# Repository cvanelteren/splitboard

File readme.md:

# Table of Contents

1.  [Welcome to Splitboard](#orge151485)
2.  [Features](#orgcb3fcca)
3.  [Know projects](#org8324adf)

# Welcome to Splitboard

Keyboard firmware written for the  esp32. I wanted to have a
bluetooth  split  keyboard  for  a while  so  I  wrote  this
firmware. The software takes  heavy inspiration from the [QMK
firmware](https://docs.qmk.fm/#/), and was developed using Platformio.

# Features

-   [X] Split communication over esp<sub>now</sub>
-   [X] Layer support
    -   Up to 16 layers
-   [X] LED support through [FastLED](https://github.com/FastLED)
-   [X] OLED support through [U8G2](https://github.com/olikraus/u8g2)
-   [X] Layer tap functionality
    -   Tap for keycode, hold for layer switch
-   [ ] Space cadet keys
    -   Shift when tapped, shift was modifier.

# Know projects

-   [Elanor](https://github.com/cvanelteren/Elanor)

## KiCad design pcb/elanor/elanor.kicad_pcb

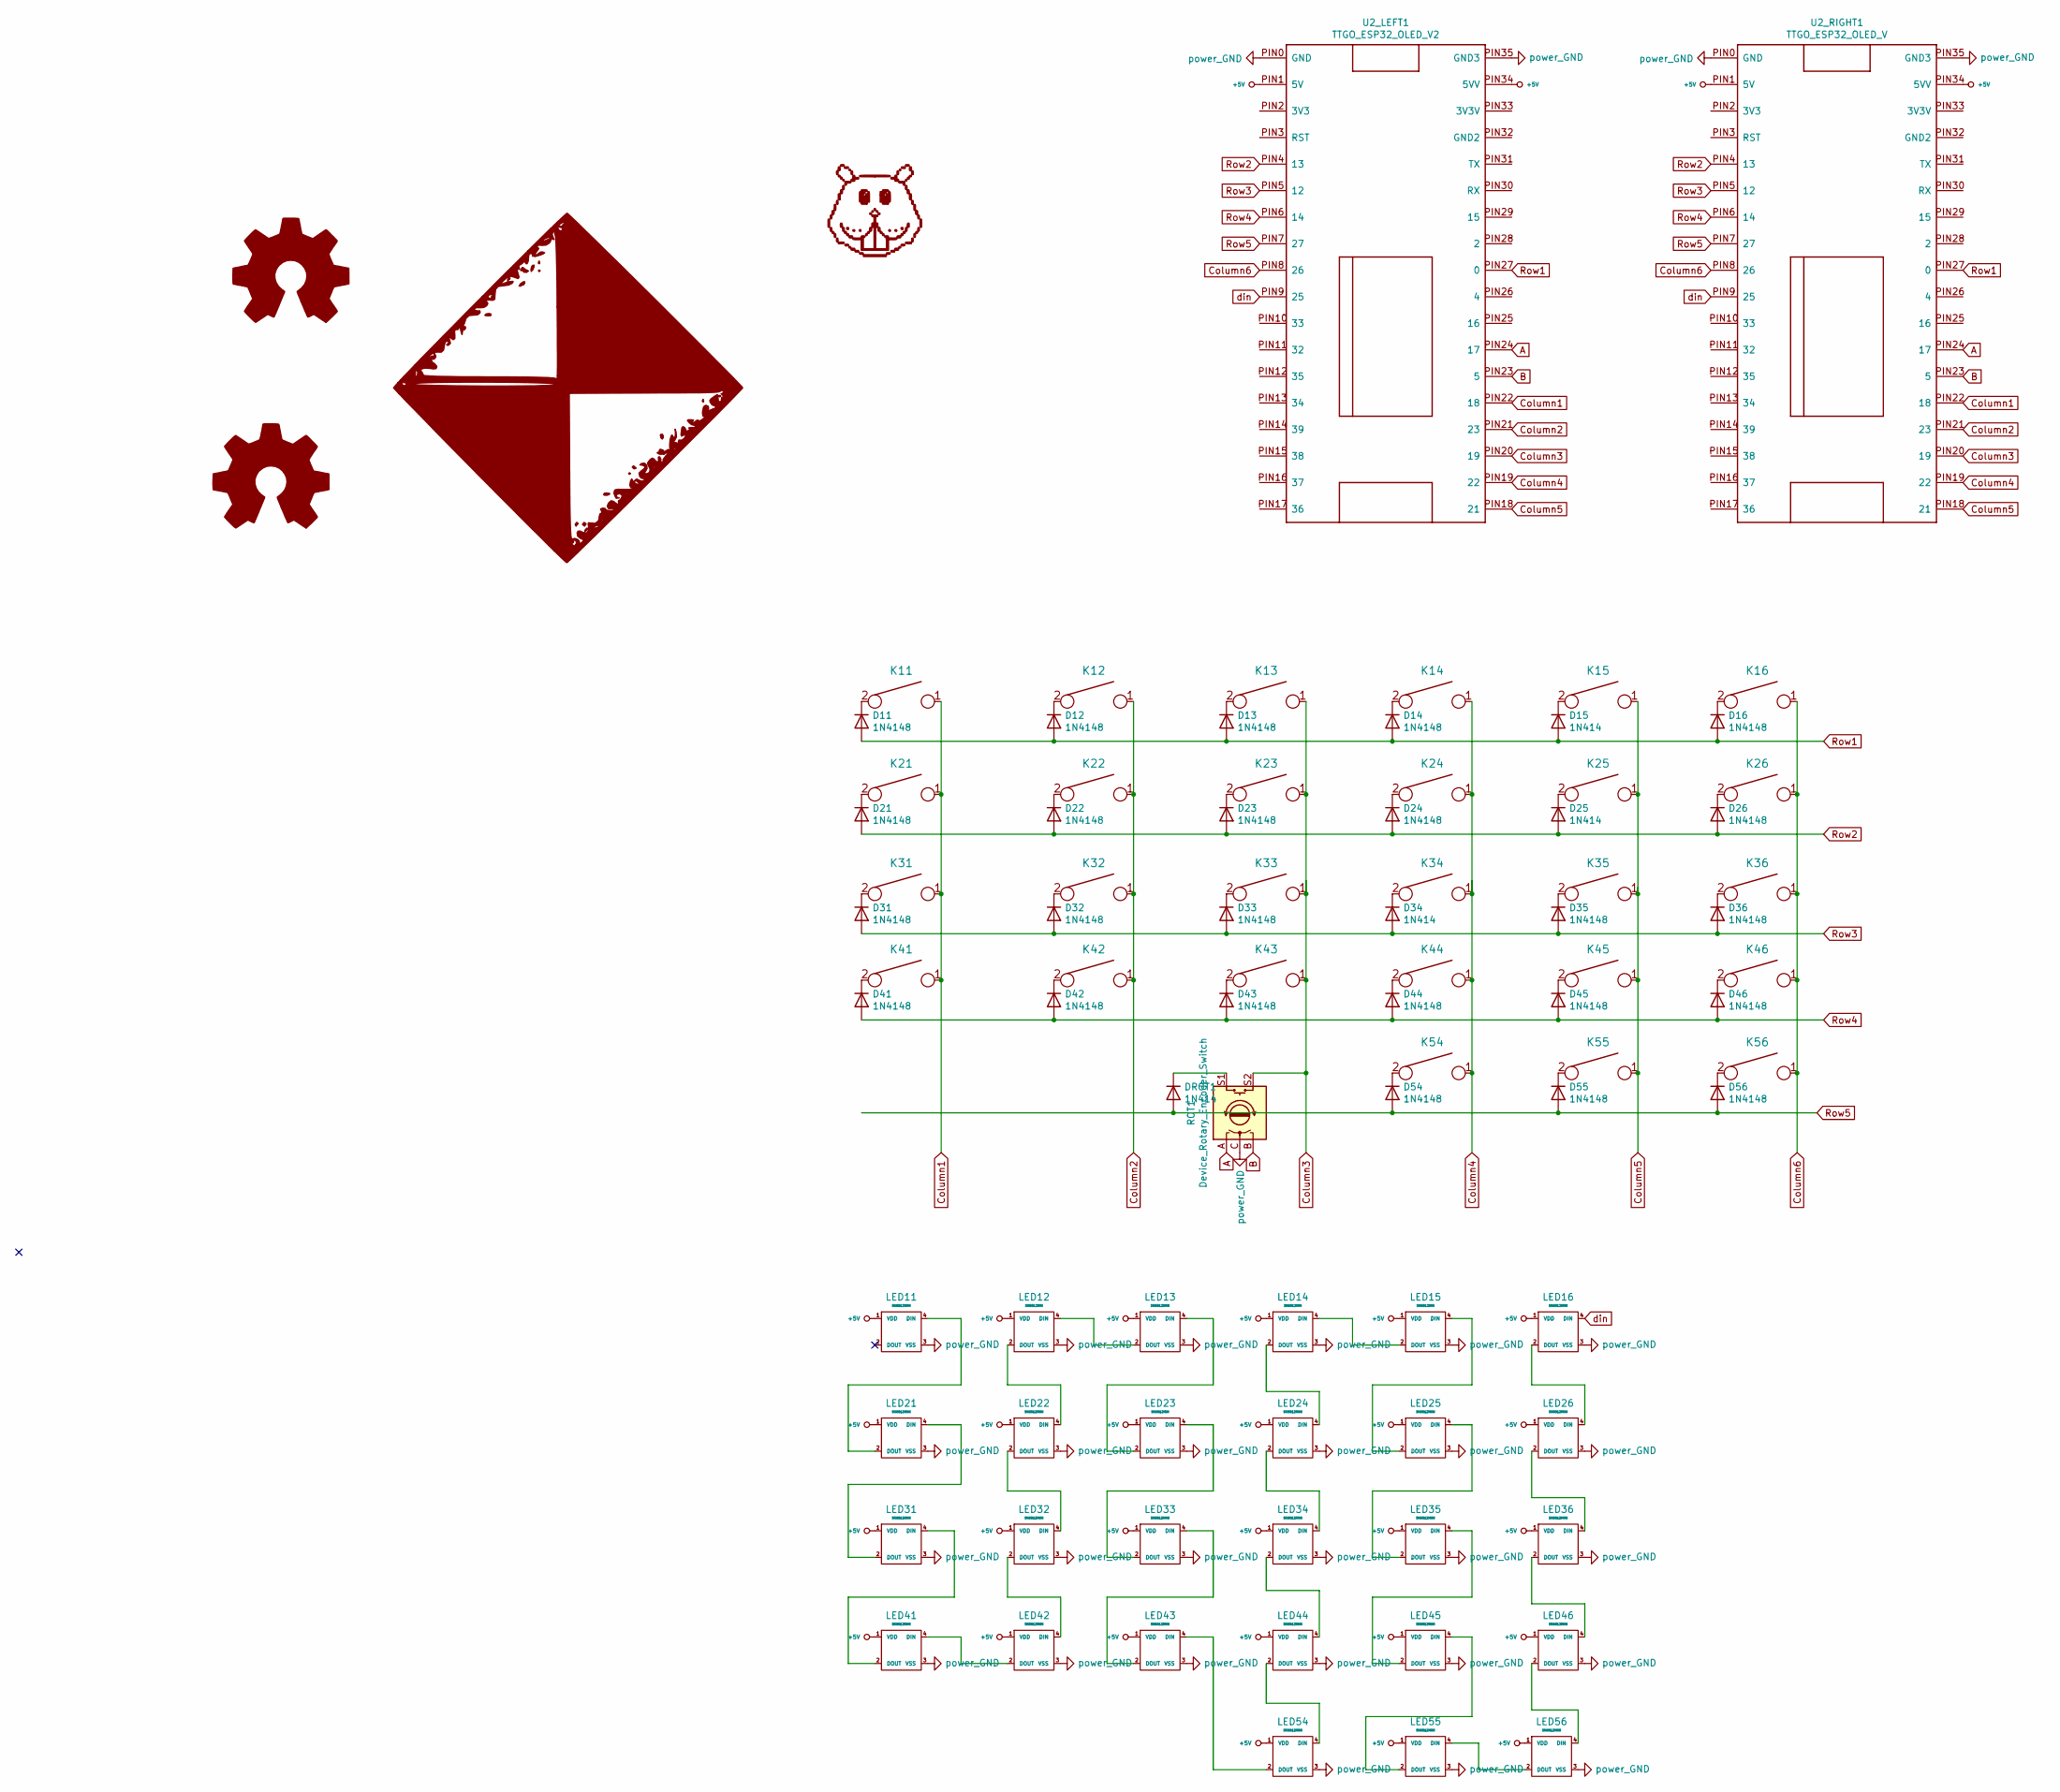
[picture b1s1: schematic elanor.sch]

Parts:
BOARD_LOGO1: LOGO; cve_logo_neg
D11, D12, D13, D14, D16, D21, D22, D23, D24, D26, D31, D32, D33, D35, D36, D41, D42, D43, D44, D45, D46, D54, D55, D56: 1N4148; D3_TH_SMD_v2
D15, D25, D34: 1N414; D3_TH_SMD_v2
DROT1: 1N414; D3_TH_SMD_v2
K11, K12, K13, K14, K15, K16, K21, K22, K23, K24, K25, K26, K31, K32, K33, K34, K35, K36, K41, K42, K43, K44, K45, K46, K54: key; CherryMX_MidHeight_Hotswap_ME
K55: key; CherryMX_MidHeight_Hotswap1.25v
K56: key; CherryMX_MidHeight_Hotswap1.5v
LED11, LED13, LED16, LED21, LED22, LED24, LED25, LED26, LED31, LED32, LED33, LED34, LED35, LED36, LED41, LED42, LED43, LED44, LED45, LED46, LED54, LED55, LED56: SK6812MINI; SK6812_double_sided_no_hole
LED12, LED14, LED15, LED23: SK6812MIN; SK6812_double_sided_no_hole
ROT1: Device_Rotary_Encoder_Switch; RotaryEncoder_Alps_EC11E-Switch_Vertical_H20mm
U2_LEFT1: TTGO_ESP32_OLED_V2; ESP32_TTGO_V2
U2_RIGHT1: TTGO_ESP32_OLED_V; ESP32_TTGO_V2
beaver1: FL; beaver_fiona

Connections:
+5V: LED11.1 (VDD), LED12.1 (VDD), LED13.1 (VDD), LED14.1 (VDD), LED15.1 (VDD), LED16.1 (VDD), LED21.1 (VDD), LED22.1 (VDD), LED23.1 (VDD), LED24.1 (VDD), LED25.1 (VDD), LED26.1 (VDD), LED31.1 (VDD), LED32.1 (VDD), LED33.1 (VDD), LED34.1 (VDD), LED35.1 (VDD), LED36.1 (VDD), LED41.1 (VDD), LED42.1 (VDD), LED43.1 (VDD), LED44.1 (VDD), LED45.1 (VDD), LED46.1 (VDD), LED54.1 (VDD), LED55.1 (VDD), LED56.1 (VDD), U2_LEFT1.PIN1 (5V), U2_LEFT1.PIN34 (5VV), U2_RIGHT1.PIN1 (5V), U2_RIGHT1.PIN34 (5VV)
A: ROT1.A, U2_LEFT1.PIN24 (17), U2_RIGHT1.PIN24 (17)
B: ROT1.B, U2_LEFT1.PIN23 (5), U2_RIGHT1.PIN23 (5)
Column1: K11.1, K21.1, K31.1, K41.1, U2_LEFT1.PIN22 (18), U2_RIGHT1.PIN22 (18)
Column2: K12.1, K22.1, K32.1, K42.1, U2_LEFT1.PIN21 (23), U2_RIGHT1.PIN21 (23)
Column3: K13.1, K23.1, K33.1, K43.1, ROT1.S2, U2_LEFT1.PIN20 (19), U2_RIGHT1.PIN20 (19)
Column4: K14.1, K24.1, K34.1, K44.1, K54.1, U2_LEFT1.PIN19 (22), U2_RIGHT1.PIN19 (22)
Column5: K15.1, K25.1, K35.1, K45.1, K55.1, U2_LEFT1.PIN18 (21), U2_RIGHT1.PIN18 (21)
Column6: K16.1, K26.1, K36.1, K46.1, K56.1, U2_LEFT1.PIN8 (26), U2_RIGHT1.PIN8 (26)
GND: LED11.3 (VSS), LED12.3 (VSS), LED13.3 (VSS), LED14.3 (VSS), LED15.3 (VSS), LED16.3 (VSS), LED21.3 (VSS), LED22.3 (VSS), LED23.3 (VSS), LED24.3 (VSS), LED25.3 (VSS), LED26.3 (VSS), LED31.3 (VSS), LED32.3 (VSS), LED33.3 (VSS), LED34.3 (VSS), LED35.3 (VSS), LED36.3 (VSS), LED41.3 (VSS), LED42.3 (VSS), LED43.3 (VSS), LED44.3 (VSS), LED45.3 (VSS), LED46.3 (VSS), LED54.3 (VSS), LED55.3 (VSS), LED56.3 (VSS), ROT1.C, U2_LEFT1.PIN0 (GND), U2_LEFT1.PIN35 (GND3), U2_RIGHT1.PIN0 (GND), U2_RIGHT1.PIN35 (GND3)
unnamed: D11.1 (K), K11.2
unnamed: D12.1 (K), K12.2
unnamed: D13.1 (K), K13.2
unnamed: D14.1 (K), K14.2
unnamed: D15.1 (K), K15.2
unnamed: D16.1 (K), K16.2
unnamed: D21.1 (K), K21.2
unnamed: D22.1 (K), K22.2
unnamed: D23.1 (K), K23.2
unnamed: D24.1 (K), K24.2
unnamed: D25.1 (K), K25.2
unnamed: D26.1 (K), K26.2
unnamed: D31.1 (K), K31.2
unnamed: D32.1 (K), K32.2
unnamed: D33.1 (K), K33.2
unnamed: D34.1 (K), K34.2
unnamed: D35.1 (K), K35.2
unnamed: D36.1 (K), K36.2
unnamed: D41.1 (K), K41.2
unnamed: D42.1 (K), K42.2
unnamed: D43.1 (K), K43.2
unnamed: D44.1 (K), K44.2
unnamed: D45.1 (K), K45.2
unnamed: D46.1 (K), K46.2
unnamed: D54.1 (K), K54.2
unnamed: D55.1 (K), K55.2
unnamed: D56.1 (K), K56.2
unnamed: DROT1.1 (K), ROT1.S1
unnamed: LED11.4 (DIN), LED21.2 (DOUT)
unnamed: LED12.2 (DOUT), LED22.4 (DIN)
unnamed: LED12.4 (DIN), LED13.2 (DOUT)
unnamed: LED13.4 (DIN), LED23.2 (DOUT)
unnamed: LED14.2 (DOUT), LED24.4 (DIN)
unnamed: LED14.4 (DIN), LED15.2 (DOUT)
unnamed: LED15.4 (DIN), LED25.2 (DOUT)
unnamed: LED16.2 (DOUT), LED26.4 (DIN)
unnamed: LED21.4 (DIN), LED31.2 (DOUT)
unnamed: LED22.2 (DOUT), LED32.4 (DIN)
unnamed: LED23.4 (DIN), LED33.2 (DOUT)
unnamed: LED24.2 (DOUT), LED34.4 (DIN)
unnamed: LED25.4 (DIN), LED35.2 (DOUT)
unnamed: LED26.2 (DOUT), LED36.4 (DIN)
unnamed: LED31.4 (DIN), LED41.2 (DOUT)
unnamed: LED32.2 (DOUT), LED42.4 (DIN)
unnamed: LED33.4 (DIN), LED43.2 (DOUT)
unnamed: LED34.2 (DOUT), LED44.4 (DIN)
unnamed: LED35.4 (DIN), LED45.2 (DOUT)
unnamed: LED36.2 (DOUT), LED46.4 (DIN)
unnamed: LED41.4 (DIN), LED42.2 (DOUT)
unnamed: LED43.4 (DIN), LED54.2 (DOUT)
unnamed: LED44.2 (DOUT), LED54.4 (DIN)
unnamed: LED45.4 (DIN), LED55.2 (DOUT)
unnamed: LED46.2 (DOUT), LED56.4 (DIN)
unnamed: LED55.4 (DIN), LED56.2 (DOUT)
Row1: D11.2 (A), D12.2 (A), D13.2 (A), D14.2 (A), D15.2 (A), D16.2 (A), U2_LEFT1.PIN27 (0), U2_RIGHT1.PIN27 (0)
Row2: D21.2 (A), D22.2 (A), D23.2 (A), D24.2 (A), D25.2 (A), D26.2 (A), U2_LEFT1.PIN4 (13), U2_RIGHT1.PIN4 (13)
Row3: D31.2 (A), D32.2 (A), D33.2 (A), D34.2 (A), D35.2 (A), D36.2 (A), U2_LEFT1.PIN5 (12), U2_RIGHT1.PIN5 (12)
Row4: D41.2 (A), D42.2 (A), D43.2 (A), D44.2 (A), D45.2 (A), D46.2 (A), U2_LEFT1.PIN6 (14), U2_RIGHT1.PIN6 (14)
Row5: D54.2 (A), D55.2 (A), D56.2 (A), DROT1.2 (A), U2_LEFT1.PIN7 (27), U2_RIGHT1.PIN7 (27)
din: LED16.4 (DIN), U2_LEFT1.PIN9 (25), U2_RIGHT1.PIN9 (25)

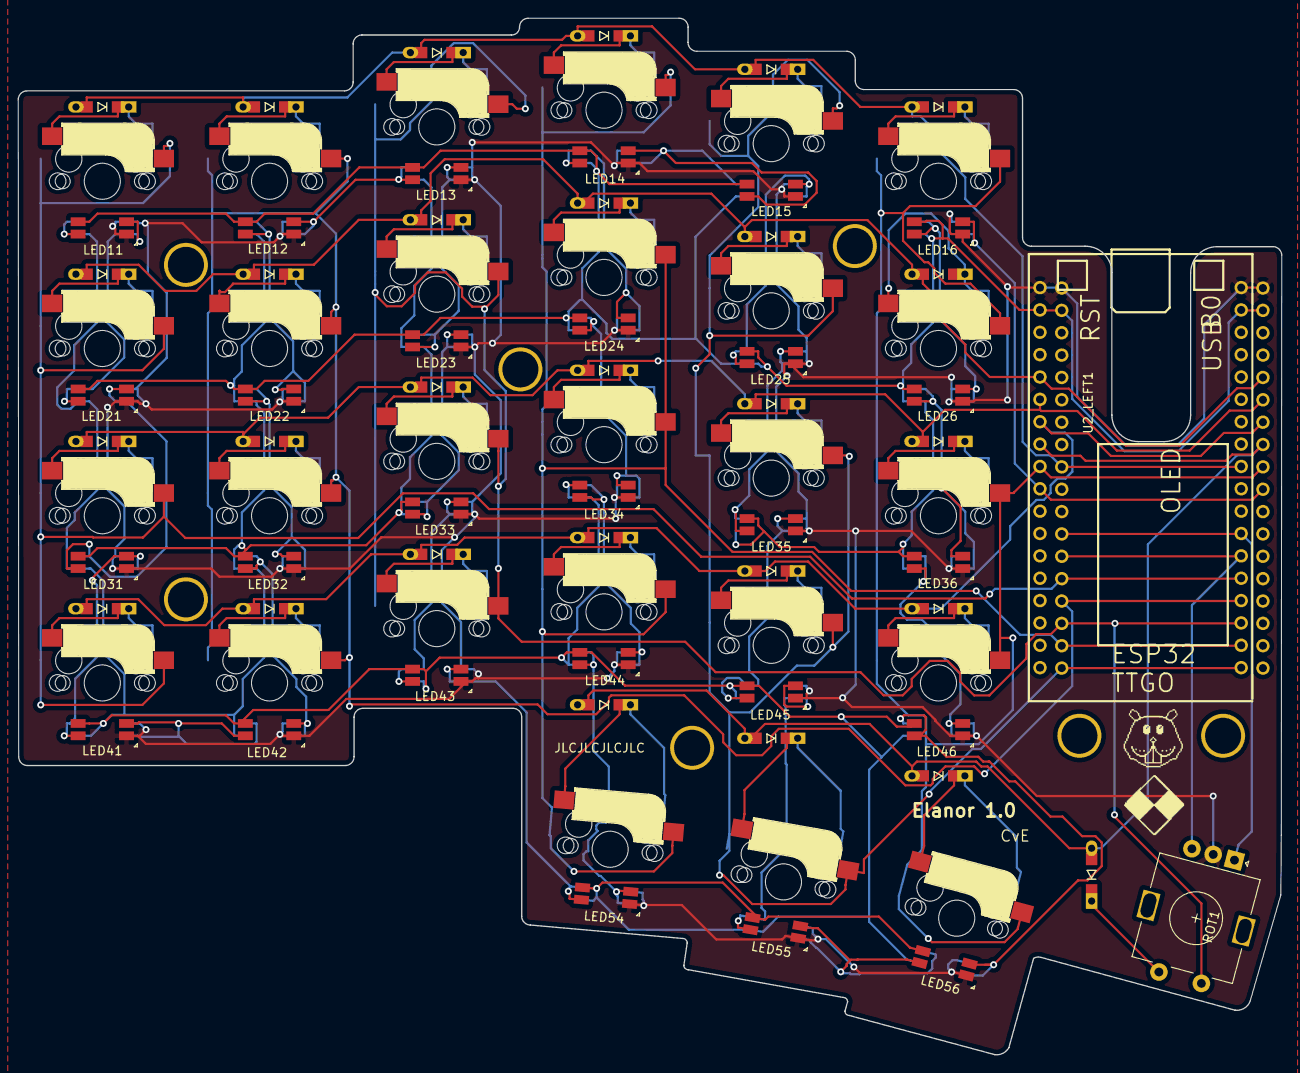
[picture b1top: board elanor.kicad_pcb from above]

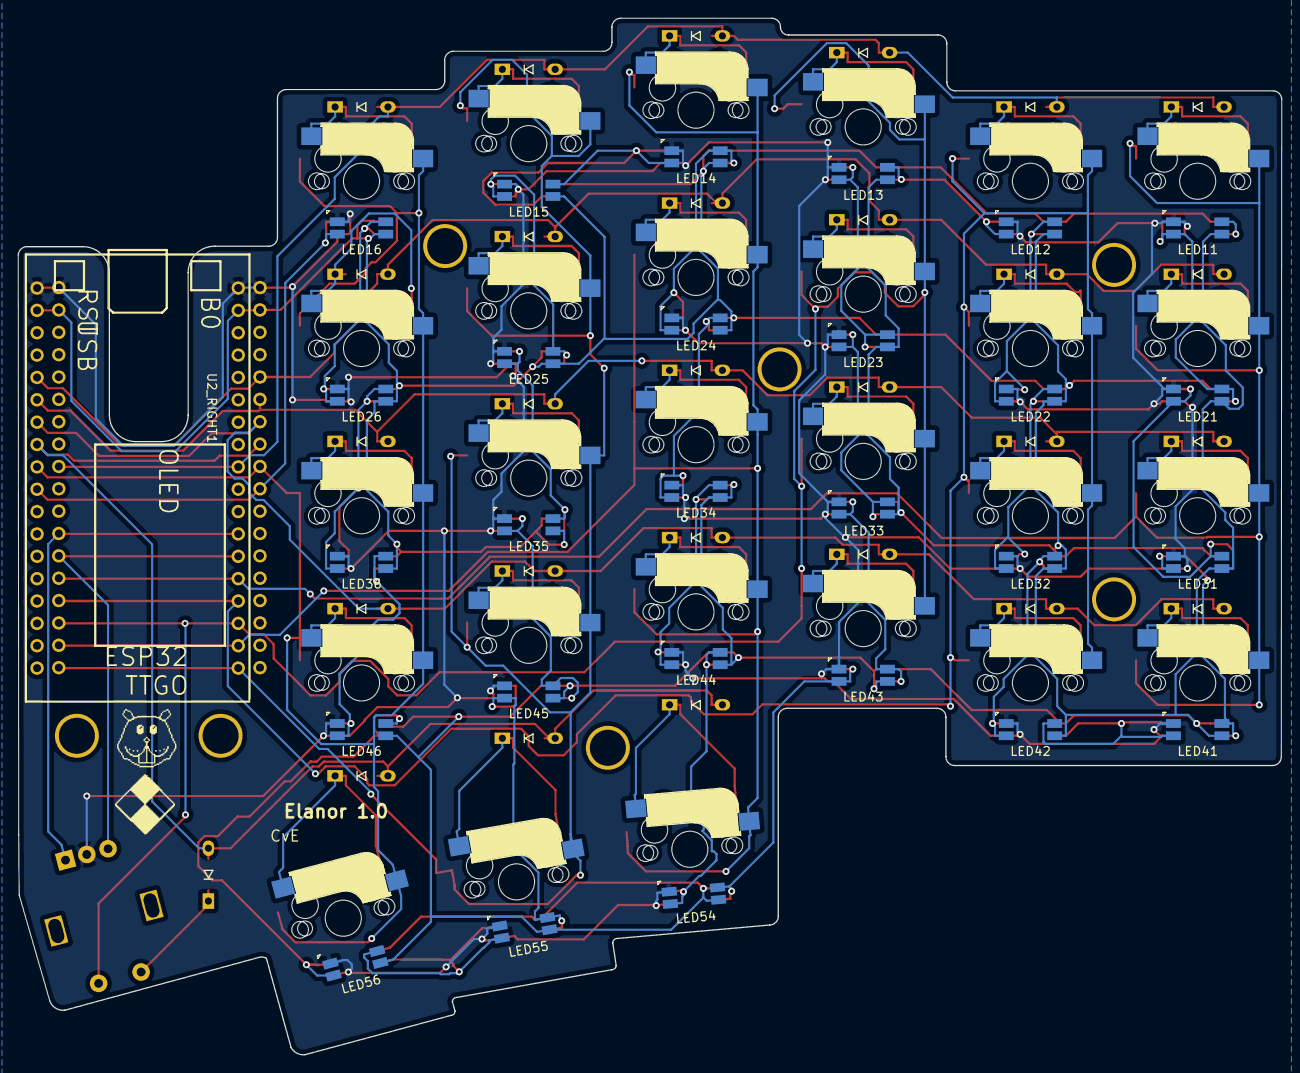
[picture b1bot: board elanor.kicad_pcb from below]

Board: 2 copper layers, 143.5 x 117.8 mm, 96 parts (3 on the bottom side), 70 nets.

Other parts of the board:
BOARD_LOGO1#2: CvE; cve_logo_neg
C11: column 5; LEGO_HOLE
C15: column3; LEGO_HOLE
C33: column 4; LEGO_HOLE
C51: column2; LEGO_HOLE
C55: column1; LEGO_HOLE
EC11: EC11; LEGO_HOLE
EC12: EC12; LEGO_HOLE
beaver1#2: FL; beaver_fiona

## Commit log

2021-04-29 all components working!
2021-07-04 working on remote_now
2021-07-04 added esp-now mesh; need to correct static variables
2021-07-04 removed logs; added basic cli
2021-07-04 added licencse
2021-07-09 removing ble
2021-07-11 working button press
2021-07-17 added merge function; broken
2021-07-26 working on press and release
2021-07-26 switches presses and releases are registered; switch was hooked wrong :P
2021-07-26 working shift key!
2021-07-30 added rotary encoder class
2021-08-08 added rotary encoder; added deep sleep
2021-08-08 removed decoder.py
2021-08-08 cleaned up repo
2021-08-08 rotary encoder now controls volume
2021-08-10 ble sending repeated keys?
2021-08-11 weird bug is gone, not sure what caused it
2021-08-16 regular update
2021-08-16 added row col for print
2021-08-16 removed determine change and buffers; replaced with bit mask
2021-08-19 starting work on esp now buffer
2021-08-20 hotfix: rotary encoder added to buffer as keyswitch
2021-08-20 added matrix unittests
2021-08-21 bump config
2021-08-21 bump
2021-08-21 Fixed esp_now mesh; added time to rotary_encoder msg
2021-08-22 New logo: introducing Elanor
2021-08-23 added ghosting unit test
2021-09-01 bump; pcb code added
2021-09-06 tested led in series; schematics are correct; starting checklist
2021-09-13 init conversion grid and idx led driver
2021-09-14 pcb files
2021-09-14 70% done with top plate
2021-09-16 init event manager
2021-09-17 mend
2021-09-17 submodule init
2021-09-17 removed ob-jupyter
2021-09-20 Added ble status
2021-09-21 Added dynamic dispatch for led driver.
2021-09-21 commit went wrong missing data
2021-09-21 added thread protection event manager; example animation and alt switches leds
2021-09-25 added a start for special keycodes processing
2021-09-27 added new readme
2021-10-06 Added configs defs; Fixed layer tap
2021-10-06 bump; various changes
2021-10-06 logo init
2021-10-19 Added new led-mode: follow-me
2021-10-19 Starting to rework actions into more cohesive interface
2021-10-19 Action represents 16bits of information. Playing around with unions
2021-10-25 - Fixed esp sleep not initializing wifi
2021-10-25 - Hotfix: rotary encoder triggering last led - Added temporary reference to config in led driver - Removed debug message for driver power down
2021-10-30 Added mod_tap keys
2021-11-16 Removed static variables into static trackers. The past method only allowed for one "move" to be made, moving between multiple layers didn't backtrack correctly.
2021-11-16 Forget to add include statement for un.map
2021-12-03 Added initial battery monitoring support
2021-12-05 Corrected parts for flash memory
2021-12-05 Initial batery monitoring support - not that accurate, maybe hardware problem
2021-12-06 forgot comment line
2021-12-07 tmp storage
2021-12-10 Initial class layout for BLE connection instead of esp_now
2021-12-10 Example program sending struct over ble
2021-12-10 Added meshclient & mesh server implementations
2021-12-10 Need to split header file into several files
2021-12-10 Various updates Prepping for esp_now replacement - removed bluetooth & client - included NimBLE and BLEKeyboard as source
2021-12-20 ready for tests
2021-12-20 Added design setup
2021-12-20 replaced mesh send with ble
2021-12-20 commited main and mesh to develop
2021-12-20 stashing
2021-12-23 Removed esp_now in mesh
2021-12-23 Added mesh number in config
2021-12-24 Restored main.cpp to normal
2021-12-24 Renamed connect to connect_to_server
2021-12-24 init static mesh buffer
2021-12-24 corrected string in log for onResult``
2021-12-24 Removed unnecessary class definitions in mesh header
2021-12-24 Corrected size of buffer for communication
2021-12-24 Making repo dependent on NIMBLE
2021-12-26 Added some design comments in mesh
2021-12-26 Logging statement for mesh
2021-12-26 Initial setup pin confirm mesh server client
2021-12-26 Added set_mode to led driver
2021-12-26 started work on event types
2021-12-27 Added event to keyboard as property
2021-12-27 Added brightness inc/dec functions
2021-12-27 Simplified the events to function with extern
2021-12-27 Removed some redundant sections in keyboard.cpp
2021-12-27 Removed redundant code in matrix.cpp
2021-12-27 Added guard to mesh when creating service
2021-12-27 Fixed memcpy for std::vector in notify_cb
2021-12-27 Added keyboard events
2021-12-27 Started work on mesh event processing. TODO: add another characteristic holding the event state.
2021-12-29 Added event characteristic Added preliminary keyboard events
2021-12-29 Templated notification of events & keys. Removed eventmanager from main
2022-01-07 Working bluetooth mesh
2022-02-16 Initial implementation of ESP now replacement
2022-12-09 updated banner
2022-12-09 update banner
2022-12-09 updated submodule
2023-04-25 uploaded initial doc
2023-04-25 Added some text to the docs.
2023-06-20 Removed unused dependencies and moved everything within Platformio
2023-06-20 Removed unused code from led and event manager
2023-06-20 Battery level can now be viewed on screen
